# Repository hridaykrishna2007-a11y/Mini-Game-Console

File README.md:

# Mini-Game-Console

## ***Small handheld game console, it runs on an arduino nano!***
This small DIY console is designed to make teens learn how to build real hardware projects, play games and teach them how to code.  
It runs on an arduino nano and takes power from a usb power source. It has 4 Mechanical CherryMX keyboard switches as the controller buttons. and a 128x64 OLED display!  

## ***PCB Design & Assembly***

This is a 2 layer PCB with dimentions of 99.40x77.02 mm.  

**PCB FILES HERE:** [Link](https://github.com/hridaykrishna2007-a11y/Mini-Game-Console/tree/main/PCB)

## ***Schematics***  

## ***PCB Design***
.png)  

## Why it was made?
This Project was made for Horizons arcana in singapore ! ( THANK YOU HACK CLUB <3 )

## HOW TO BUILD THIS PROJECT:  
Easy Peasy.
- Order the parts from the BOM and get the case and the keycaps 3d printed and ready.
- Solder the parts on the pcb and keep the orientations in mind (or you are cooked).
- Superglue the case together. (This project is designed keeping portablity and light weight in mind. Hence no screws as it will increase the weight)
- Purchase or 3d print some keycaps (here's one: https://www.printables.com/model/118708-simple-cherry-mx-keycap)
- upload your code (or the sample one in this same repo) using usb cable and arduino ide.
- connec to a power source like a powerbank.
- PLAYYYYYYYY!!!!!!

https://github.com/user-attachments/assets/bd86371d-4319-4f34-b711-88d048939bdb

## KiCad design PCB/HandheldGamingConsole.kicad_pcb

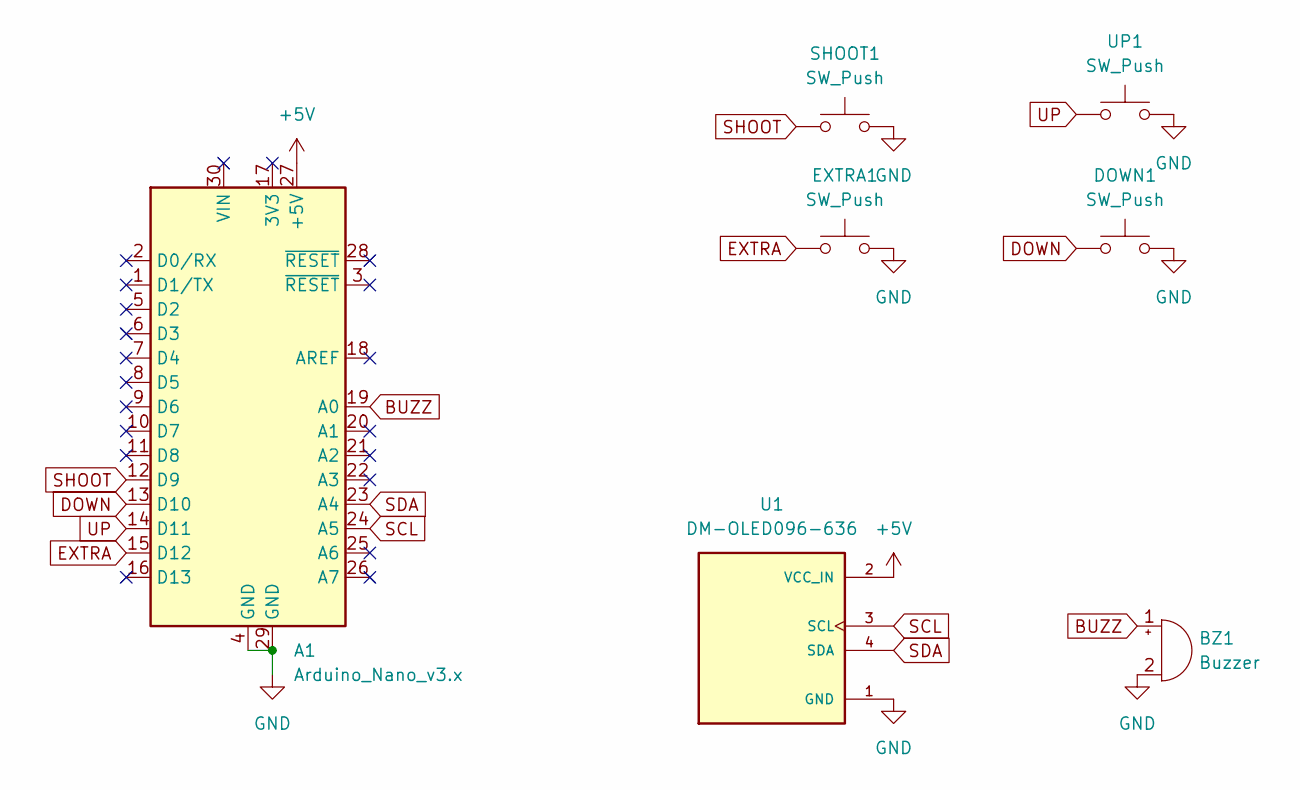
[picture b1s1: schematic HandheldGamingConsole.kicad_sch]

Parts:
A1: Arduino_Nano_v3.x; Arduino_Nano
BZ1: Buzzer; XDCR_KXG1203C
DOWN1: SW_Push; SW_Cherry_MX_1.00u_PCB
EXTRA1: SW_Push; SW_Cherry_MX_1.00u_PCB
SHOOT1: SW_Push; SW_Cherry_MX_1.00u_PCB
U1: DM-OLED096-636; MODULE_DM-OLED096-636; PARTREV 2018-09-10
UP1: SW_Push; SW_Cherry_MX_1.00u_PCB

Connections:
+5V: A1.27 (+5V), U1.2 (VCC_IN)
BUZZ: A1.19 (A0), BZ1.1 (+)
DOWN: A1.13 (D10), DOWN1.1
EXTRA: A1.15 (D12), EXTRA1.1
GND: A1.4 (GND), A1.29 (GND), BZ1.2 (-), DOWN1.2, EXTRA1.2, SHOOT1.2, U1.1 (GND), UP1.2
SCL: A1.24 (A5), U1.3 (SCL)
SDA: A1.23 (A4), U1.4 (SDA)
SHOOT: A1.12 (D9), SHOOT1.1
UP: A1.14 (D11), UP1.1

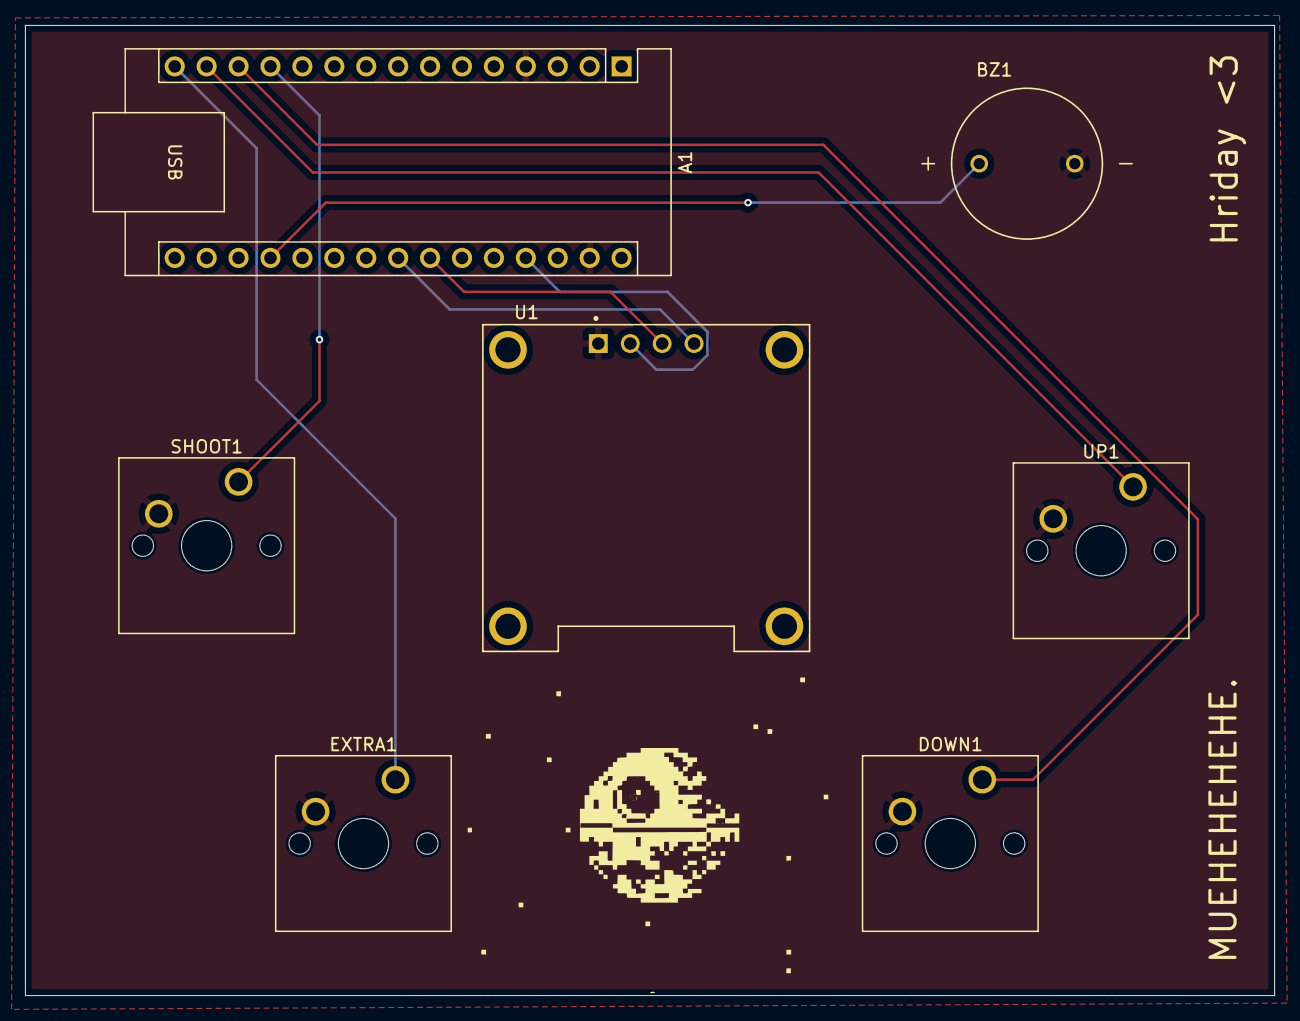
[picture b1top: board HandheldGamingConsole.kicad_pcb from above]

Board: 2 copper layers, 99.4 x 77.2 mm, 7 parts (0 on the bottom side), 9 nets.
